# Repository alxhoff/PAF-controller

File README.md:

# PAF-controller

Controller for the Personal Air Filter (PAF) system being developed at TUM EDA/RCS

## Setup 

*Note: this is the setup steps on an Arch Linux machine*

### Prereqs

From [here](https://docs.espressif.com/projects/esp-idf/en/latest/esp32/get-started/index.html#get-started-get-prerequisites):

```
sudo pacman -S --needed gcc git make flex bison gperf python-pip cmake ninja ccache dfu-util
```

Set python3 as default

```
sudo ln -sf /usr/bin/python3.7 /usr/bin/python
```

### AUR toolchain

OpenOCD and toolchain from AUR

```
yaourt gcc-xtensa-esp32-elf-bin
yaourt openocd-esp32
```

### ESP-IDF

*Note: by default the IDF install scripts place the toolchain and openocd
version into the directory `~/.espressif`, I have made the assumption that this
is where the tooling is always located in the CMake.

```
mkdir ~/esp 
cd ~/esp
git clone --recursive https://github.com/espressif/esp-idf.git
cd esp-idf
./install.sh
```

#### Python Packages

I had troubles installing proper versions of certain packages to satisfy the 
IDF's dependencies. Namely the packages `pygdbmi` and `gdbgui`.

To fix such dependencies manually uninstall the packages using `pip`

```
pip uninstall pygdbmi
```

and then install the specific version required (given by IDF script output)

```
pip install -I pygdbmi==0.9.0.2
```

You might need to play with the order in which you install the packages as those with
dependencies might install the others and with a incorrect version.

### Environment Variables 

```
. $HOME/esp/esp-idf/export.sh
```

Make sure you're using bash.

## Test Build

```
cd $HOME/esp/esp-idf/examples/wifi/scan
make menuconfig #Configure SDK options
make flash monitor #With device plugged in it should appear as /dev/ttyUSB0)
```

## Building Project

```
mkdir build
cd build
cmake ..
make
```

## Debugging Using JLink

```
make debug
```

Additionally you can specify your own OpenOCD version to use using `-DESP_OPENOCD`.
This for instance can be used to use the AUR OpenOCD version, although CMake first
checks if this version of OpenOCD has been installed before searching for the
toolchain version in `~/espressif`.

## Flashing

```
make flash
```

## Connecting to UART

The IDF provides an easy to use UART "monitor" that can be used by appending
monitor to the target, ie. `make flash monitor`

Otherwise it can be used as its own target

```
make monitor
```

## Additional Targets

### Astyle Format

```
cmake -DENABLE_ASTYLE=ON ..
make format
```

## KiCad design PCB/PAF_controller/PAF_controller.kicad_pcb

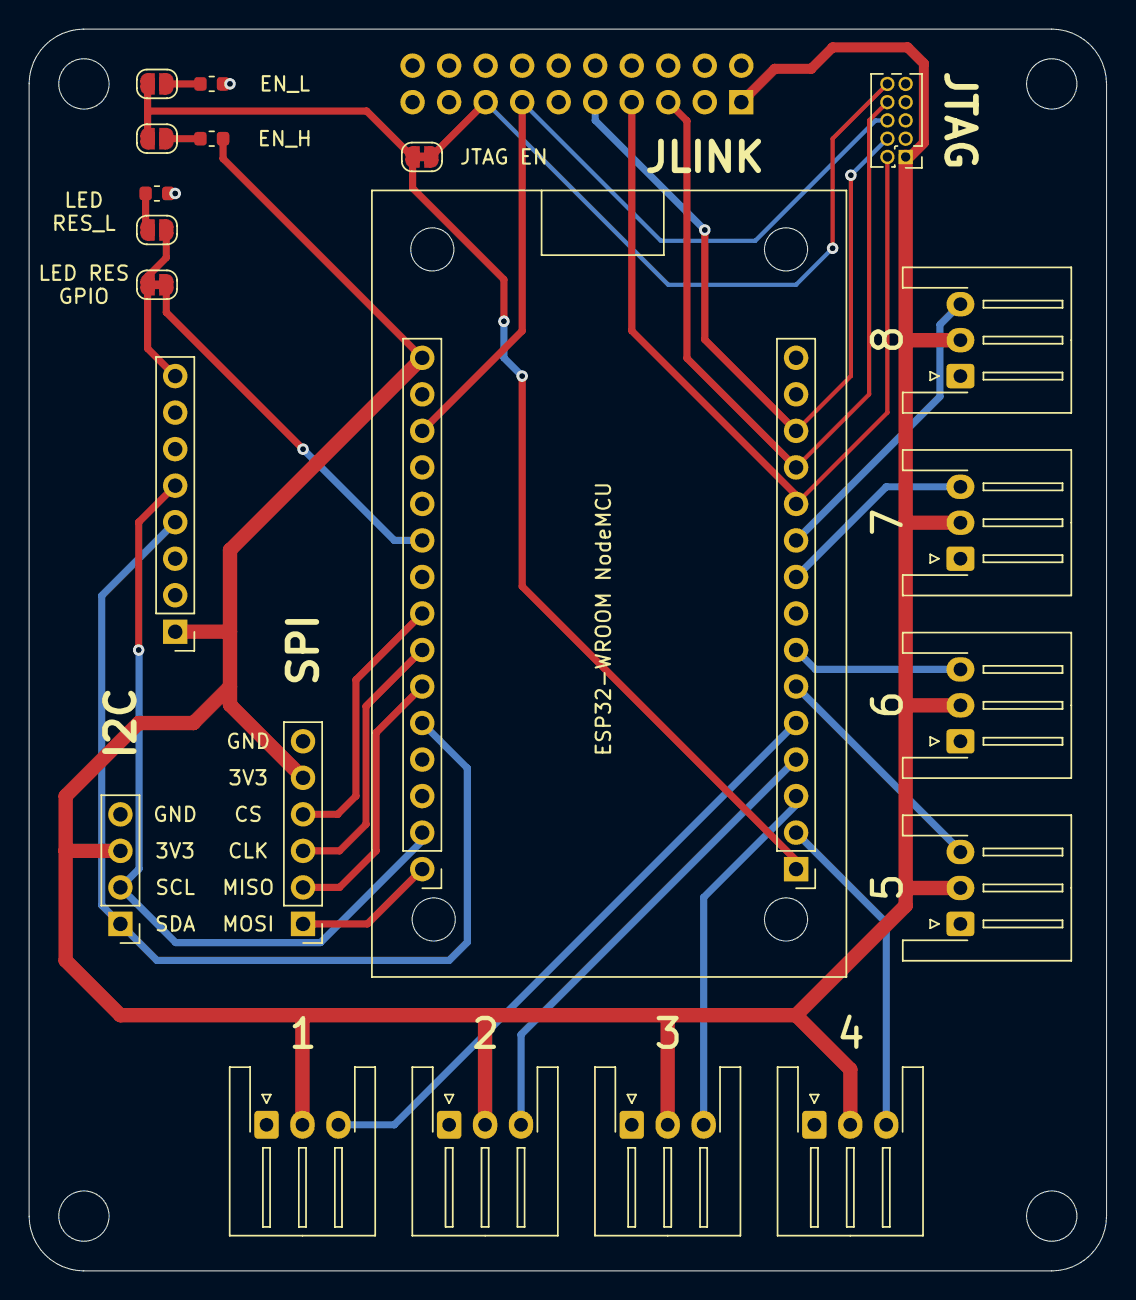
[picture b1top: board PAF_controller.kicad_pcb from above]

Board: 2 copper layers, 74.9 x 86.4 mm, 22 parts (1 on the bottom side), 27 nets.

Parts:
E1: ESP32-WROOM-NODEMCU
J1: Conn_02x05_Odd_Even; PinHeader_2x05_P1.27mm_Vertical
J2: Conn_02x10_Odd_Even; PinHeader_2x10_P2.54mm_Horizontal
J3: Conn_01x06; PinHeader_1x06_P2.54mm_Vertical
J4: Conn_01x04; PinHeader_1x04_P2.54mm_Vertical
J5: Conn_01x08; PinHeader_1x08_P2.54mm_Vertical
J6, J7, J8, J9, J10, J11, J12, J13: Conn_01x03; JST_XH_S3B-XH-A-1_1x03_P2.50mm_Horizontal
JP1, JP2, JP5: SolderJumper_2_Open; SolderJumper-2_P1.3mm_Open_RoundedPad1.0x1.5mm
JP3, JP4: SolderJumper_2_Bridged; SolderJumper-2_P1.3mm_Bridged_RoundedPad1.0x1.5mm
R1, R2, R3: R_Small; R_0603_1608Metric

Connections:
Debug_TCK: E1.13, J1.4, J2.9
Debug_TDI: E1.12, J1.8, J2.5
Debug_TDO: E1.18, J1.6, J2.13
Debug_TMS: E1.11, J1.2, J2.7
GND: E1.14, E1.17, J1.3, J1.5, J1.9, J2.4, J2.6, J2.8, J2.10, J2.12, J2.14, J2.16, J2.18, J2.20, J3.6, J4.4, J5.2, J6.1, J7.1, J8.1, J9.1, J10.1, J11.1, J12.1, J13.1, R1.2, R3.2
I2C_SCL: E1.29, J4.2, J5.5
I2C_SDA: E1.26, J4.1, J5.4
LED_PORT_PWR: E1.16, J1.1, J2.1, J3.5, J4.3, J5.1, J6.2, J7.2, J8.2, J9.2, J10.2, J11.2, J12.2, J13.2, R2.2
LED_PWM_1: E1.5, J10.3
LED_PWM_2: E1.4, J9.3
LED_PWM_3: E1.3, J12.3
LED_PWM_4: E1.2, J8.3
LED_PWM_5: E1.6, J6.3
LED_PWM_6: E1.7, J7.3
LED_PWM_7: E1.9, J13.3
LED_PWM_8: E1.10, J11.3
unnamed: E1.1, JP1.2, JP2.2, JP3.2
unnamed: JP1.1, R2.1
unnamed: JP2.1, R3.1
unnamed: JP5.1, R1.1
OLED_RES: J5.8, JP4.2, JP5.2
RF_EN: J1.10, J2.15, JP3.1
SCREEN_RESET: E1.21, JP4.1
SPI_CLK: E1.24, J3.3
SPI_CS: E1.23, J3.4
SPI_MISO: E1.25, J3.2
SPI_MOSI: E1.30, J3.1

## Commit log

2020-08-24 Initial code
2020-08-24 Initial rough website
2020-08-25 Split up files and added format target
2020-08-25 Added rough LED code
2020-08-25 Added AP code
2020-08-25 Added inits to main
2020-08-25 Untested openocd/gdb debugging config
2020-08-26 Build system fixes
2020-08-26 Controller PCB
2020-08-26 Gerber for v1.0
2020-08-27 Small fixes to get initial code working
2020-09-01 Updated to netif and esp_http_server
2020-09-01 Fixed up GETs
2020-09-02 Webserver working
2020-09-02 Removed LED code for now
2020-09-03 Added GPIO led
2020-09-04 Fixed LED PWM
2020-09-04 Fixed POST set request handling
2020-09-04 Initial port of ssd1306 i2c code
2020-09-04 Tidying SSD1306 code
2020-09-04 i2c driver install failing
2020-09-06 Ported screen code, builds
2020-09-06 Fixing screen code errors
2020-09-07 Sketchy fix for draw_framebuffer
2020-09-07 Discarded waste hunks
2020-09-07 SSD1306 refresh works, not tested on hardware
2020-09-07 Screen seems to be working
2020-09-08 Tweaked and added some screen API stuff
2020-09-08 Added some more screen API functions
2020-09-09 Minor fixes and screen API additions
2020-09-17 Fixed bug regarding post_request
2020-09-17 Error Fixes
2020-09-17 Adding timer function to the webserver, missing set capabilities
2020-09-17 GPIO capabilities added to the code, webserver needs to be adapted
2020-09-17 Adding timer for led timing
2020-09-17 Formatting
2020-09-17 Added timer capabilities
2020-09-17 Added stream and single control bytes to SSD1306 start functions
2020-09-17 Little tweaks to GPIO code
2020-09-17 removed unused header
2020-09-17 Webpage typo fix
2020-09-17 Added contrast function for ssd1306
2020-09-22 Made ssd1306 i2c more verbose
2020-09-22 Added verbose to write command
2020-09-22 Added verbosity to i2c link creation
2020-09-22 Added more verbosity
2020-09-22 Removed stupid check
2020-09-22 more verbosity
2020-09-23 HTML fixes
2020-09-23 pre-format
2020-09-24 Some testing stuff
2020-10-12 Adding tests, do need calibration
2020-10-12 Adding spinlock to hardware counter ISR
2020-10-12 Completing paf_test_run_test func
2020-10-12 Changing label of frequency
2020-10-14 Server jQuery and Bootstrap from device instead of using internet refs
